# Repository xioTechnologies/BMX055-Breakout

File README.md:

BMX055-Breakout
===============

A simple breakout board for the [Bosch BMX055](http://www.bosch-sensortec.com/en_GB/homepage/products_3/9_axis_sensors_5/ecompass_2/bmx055_1/bmx055) for fabrication by [OSH Park](https://oshpark.com/).  Provides access to I2C pins and INT3 for gyroscope data ready interrupt.

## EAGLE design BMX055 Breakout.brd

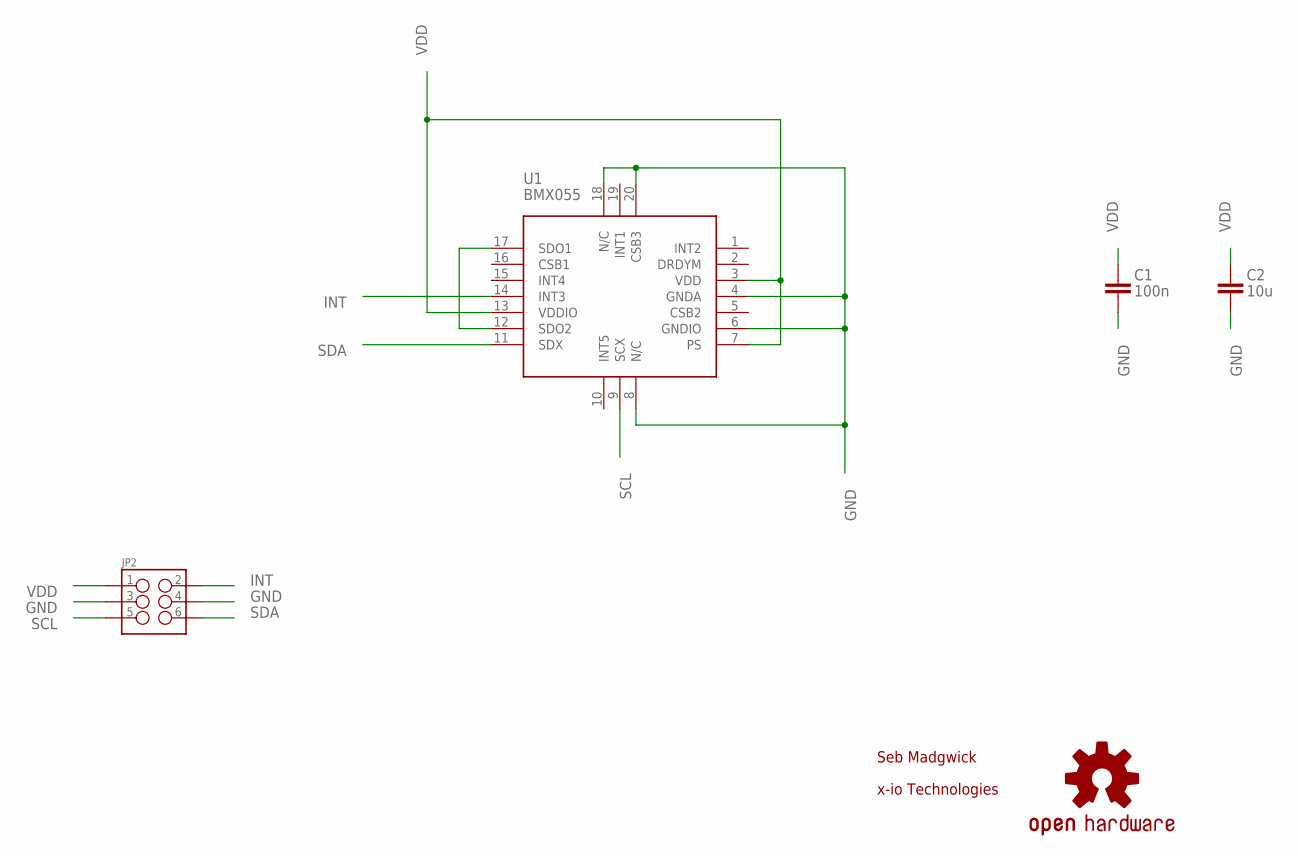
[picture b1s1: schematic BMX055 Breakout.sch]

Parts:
C1: 100n; 0603-CAP
C2: 10u; 0603-CAP
JP2: M03X2POGO_PINS; 2X3_POGO
LOGO1: OSHW-LOGOS; OSHW-LOGO-S
U1: BMX055

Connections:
GND: C1.2, C2.2, JP2.P$3 (3), JP2.P$4 (4), U1.4 (GNDA), U1.6 (GNDIO), U1.8 (N/C), U1.18 (N/C), U1.20 (CSB3)
INT: JP2.P$2 (2), U1.14 (INT3)
unnamed: U1.12 (SDO2), U1.17 (SDO1)
SCL: JP2.P$5 (5), U1.9 (SCX)
SDA: JP2.P$6 (6), U1.11 (SDX)
VDD: C1.1, C2.1, JP2.P$1 (1), U1.3 (VDD), U1.7 (PS), U1.13 (VDDIO)

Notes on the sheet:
Seb Madgwick
x-io Technologies

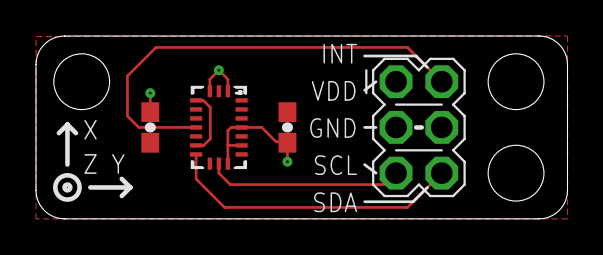
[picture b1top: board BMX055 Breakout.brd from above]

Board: 2 copper layers, 29.5 x 10.2 mm, 5 parts (1 on the bottom side), 6 nets.

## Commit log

2014-06-25 Add project files
2014-06-25 Add OSH Park images

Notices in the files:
parts and their libraries:
SparkFun-Connectors: Licensing: Creative Commons ShareAlike 4.0 International - https://creativecommons.org/licenses/by-sa/4.0
